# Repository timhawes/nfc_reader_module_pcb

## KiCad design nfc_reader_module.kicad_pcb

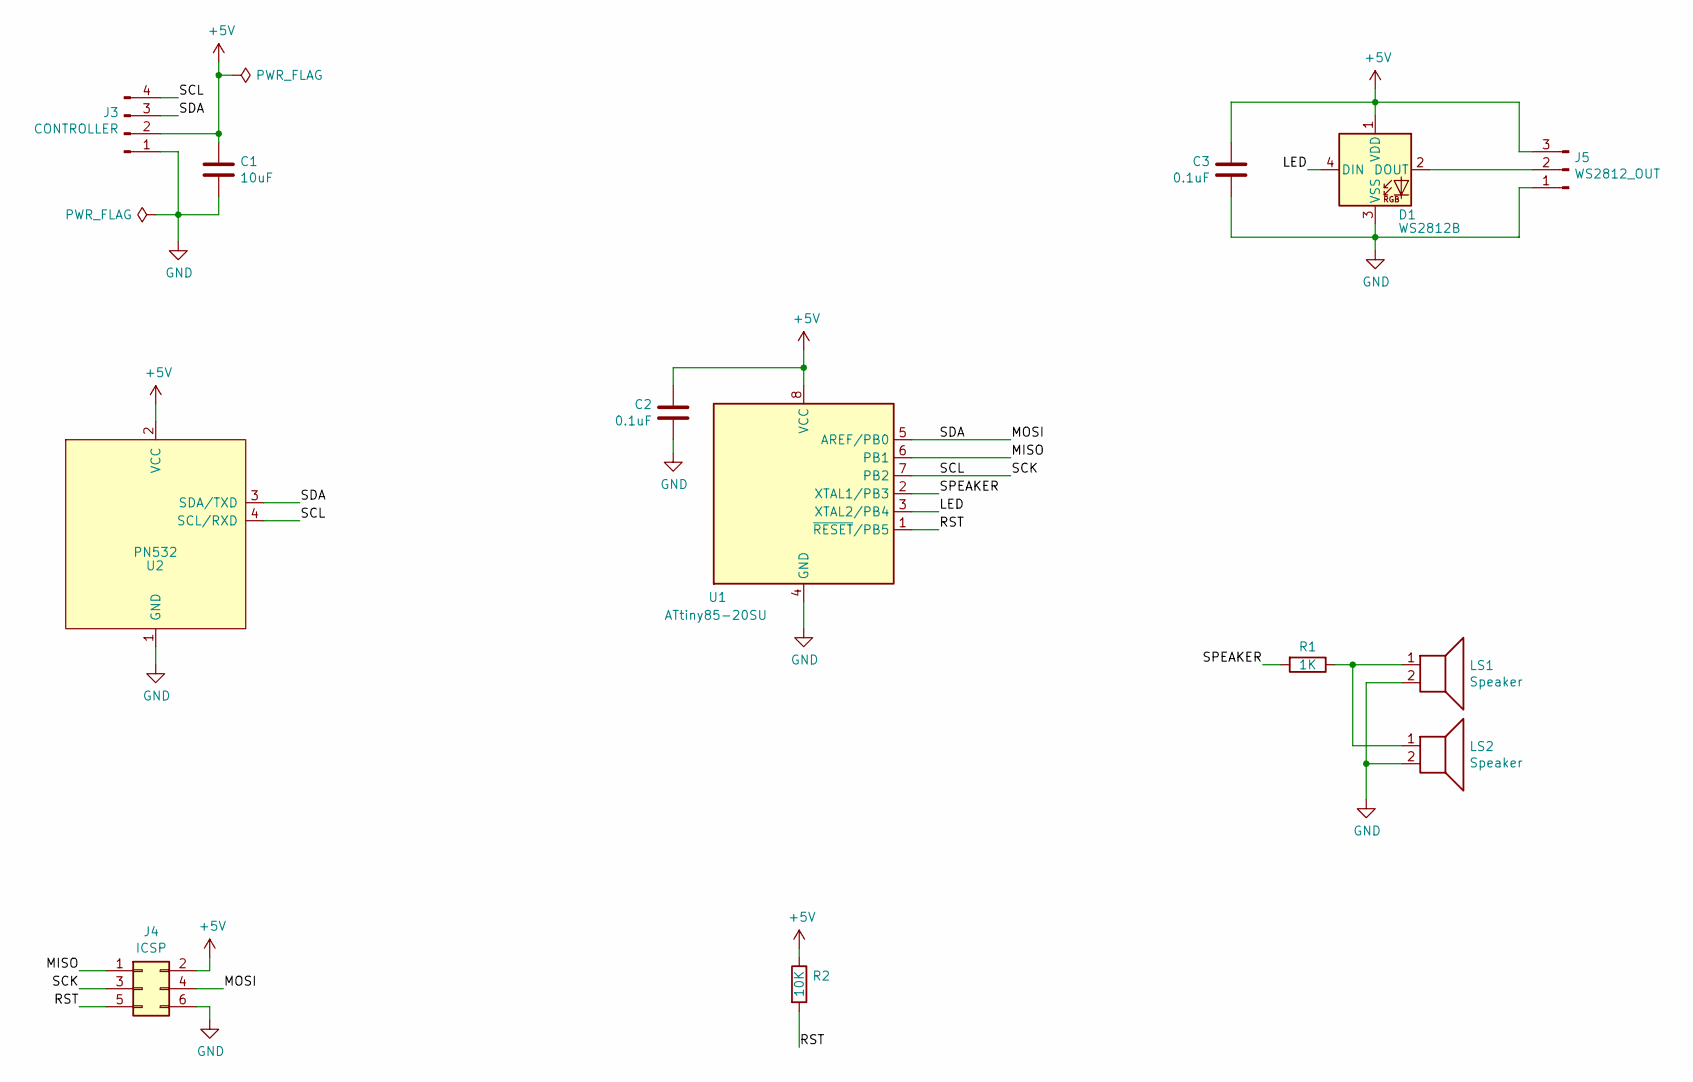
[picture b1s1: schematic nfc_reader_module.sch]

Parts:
C1: 10uF; C_0805_2012Metric
C2, C3: 0.1uF; C_0603_1608Metric
D1: WS2812B; LED_WS2812B_PLCC4_5.0x5.0mm_P3.2mm
J3: CONTROLLER; PhoenixContact_MCV_1,5_4-G-3.81_1x04_P3.81mm_Vertical
J4: ICSP; PinHeader_2x03_P2.54mm_Vertical
J5: WS2812_OUT; PinHeader_1x03_P2.54mm_Vertical
LS1: Speaker; Buzzer_Murata_PKMCS0909E4000-R1
LS2: Speaker; Buzzer_12x9.5RM7.6
R1: 1K; R_0603_1608Metric
R2: 10K; R_0603_1608Metric
U1: ATtiny85-20SU; SOIJ-8_5.3x5.3mm_P1.27mm
U2: PN532; ELECHOUSE_PN532_V4_USART_I2C

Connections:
+5V: C1.1, C2.2, C3.2, D1.1 (VDD), J3.2, J4.2, J5.3, R2.1, U1.8 (VCC), U2.2 (VCC)
/LED: D1.4 (DIN), U1.3 (XTAL2/PB4)
/MISO: J4.1, U1.6 (PB1)
/MOSI: J3.3, J4.4, U1.5 (AREF/PB0), U2.3 (SDA/TXD)
/RST: J4.5, R2.2, U1.1 (~RESET~/PB5)
/SCK: J3.4, J4.3, U1.7 (PB2), U2.4 (SCL/RXD)
/SPEAKER: R1.2, U1.2 (XTAL1/PB3)
GND: C1.2, C2.1, C3.1, D1.3 (VSS), J3.1, J4.6, J5.1, LS1.2, LS2.2, U1.4 (GND), U2.1 (GND)
unnamed: D1.2 (DOUT), J5.2
unnamed: LS1.1, LS2.1, R1.1

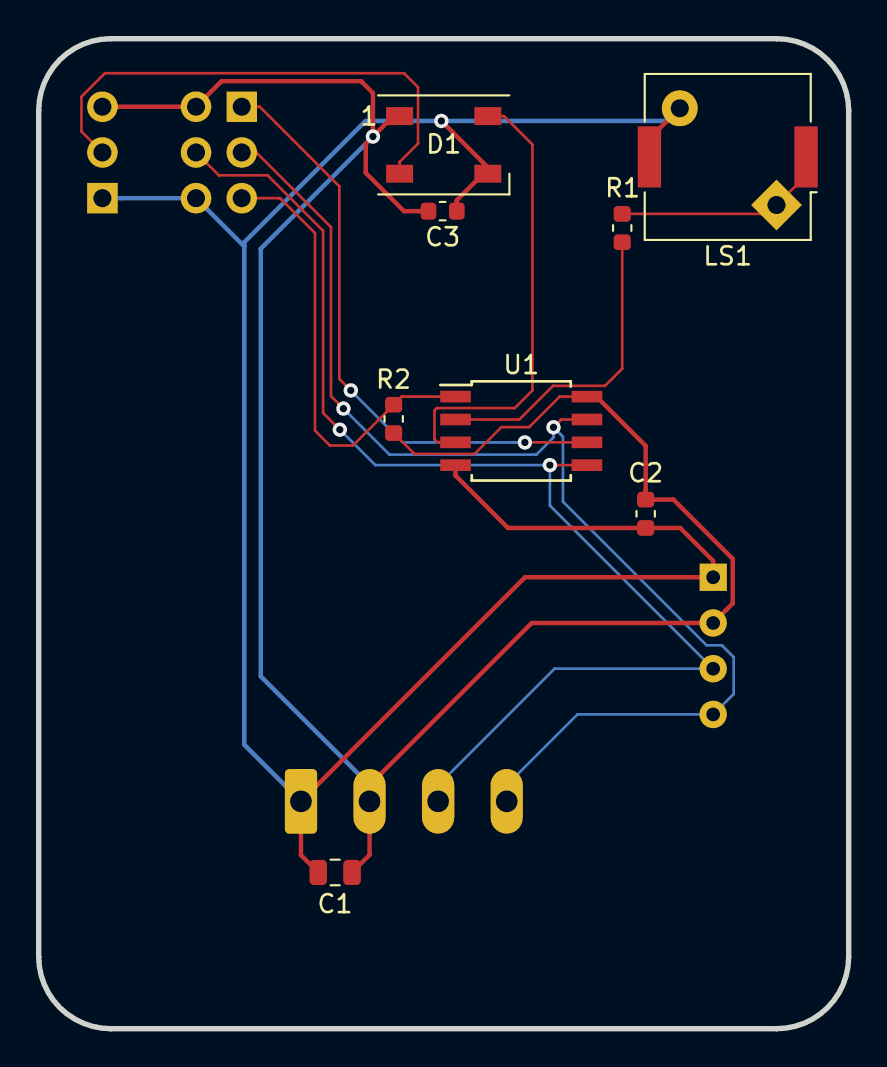
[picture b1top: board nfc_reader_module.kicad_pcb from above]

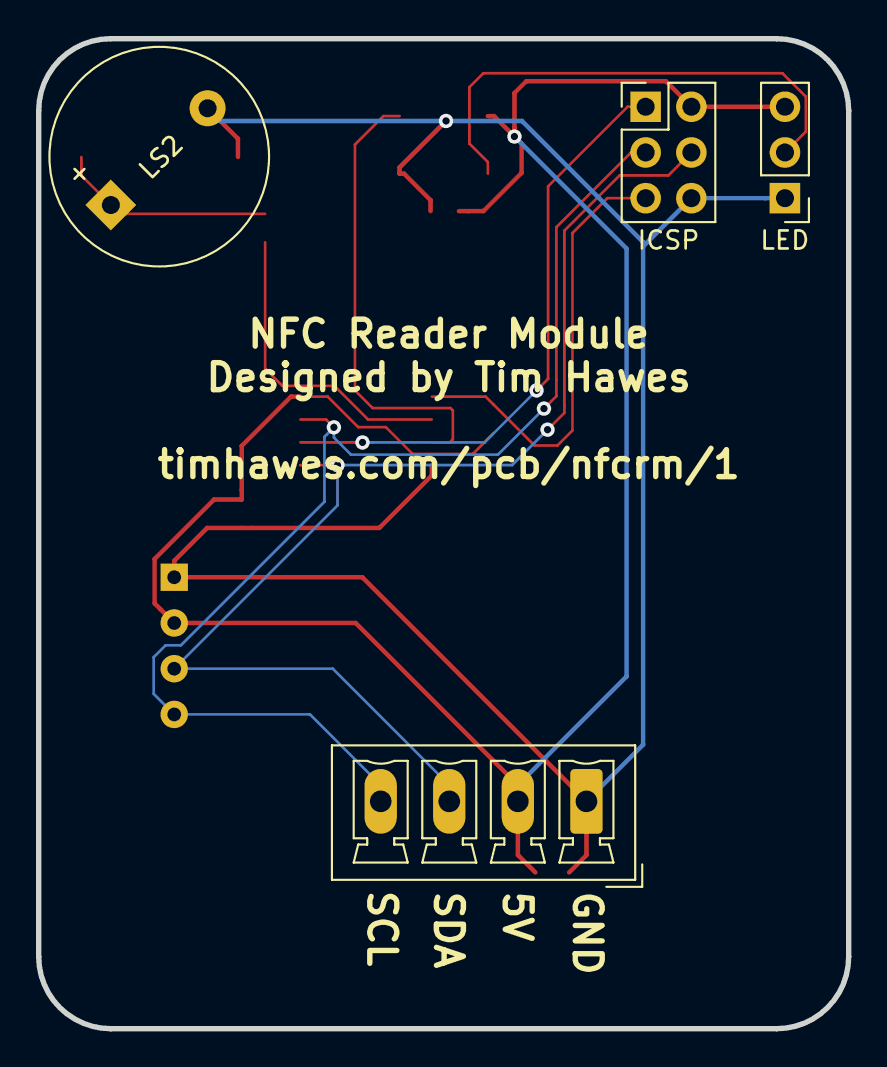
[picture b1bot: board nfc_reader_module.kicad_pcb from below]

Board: 2 copper layers, 45.0 x 55.0 mm, 14 parts (5 on the bottom side), 10 nets.

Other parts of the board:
OUTLINE_55_45_R4: Outline_55_45_R4
